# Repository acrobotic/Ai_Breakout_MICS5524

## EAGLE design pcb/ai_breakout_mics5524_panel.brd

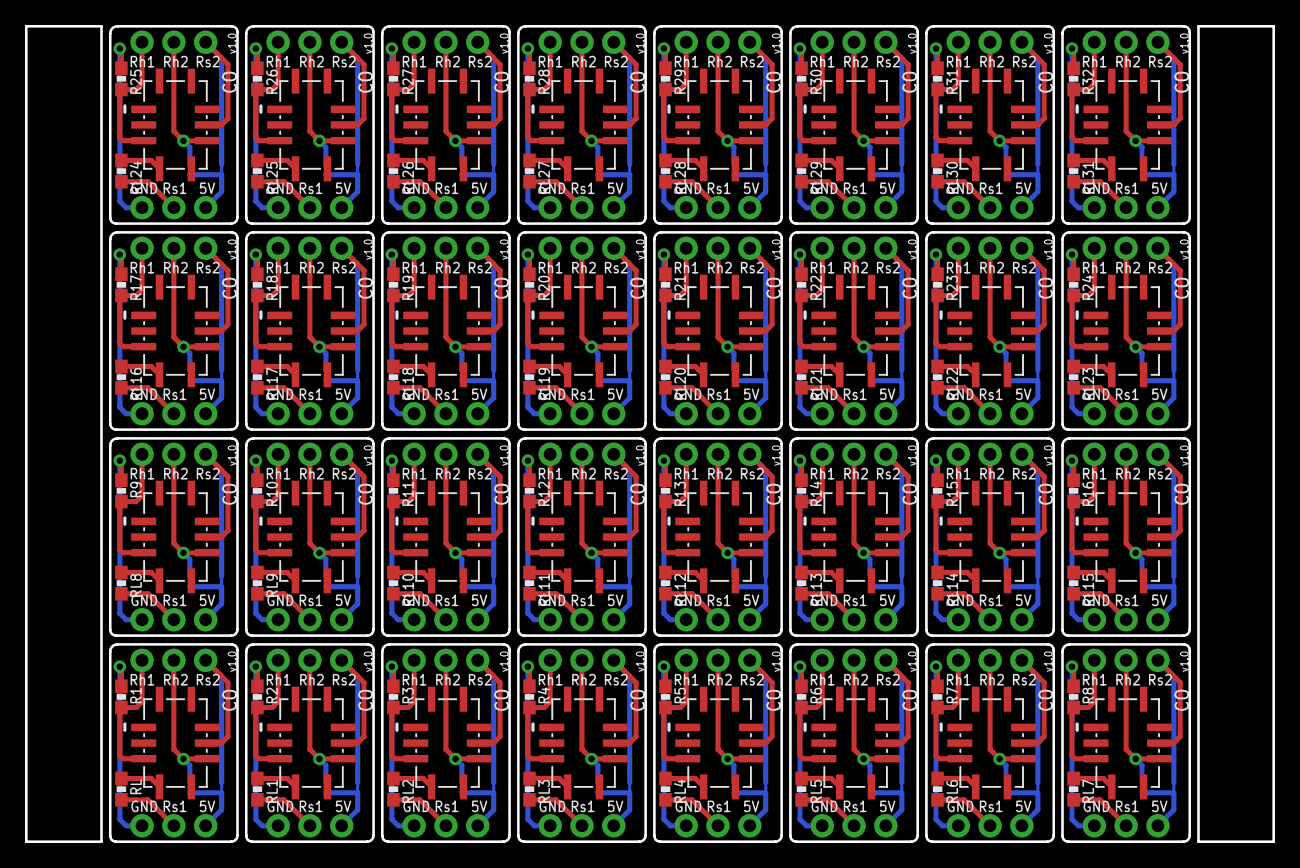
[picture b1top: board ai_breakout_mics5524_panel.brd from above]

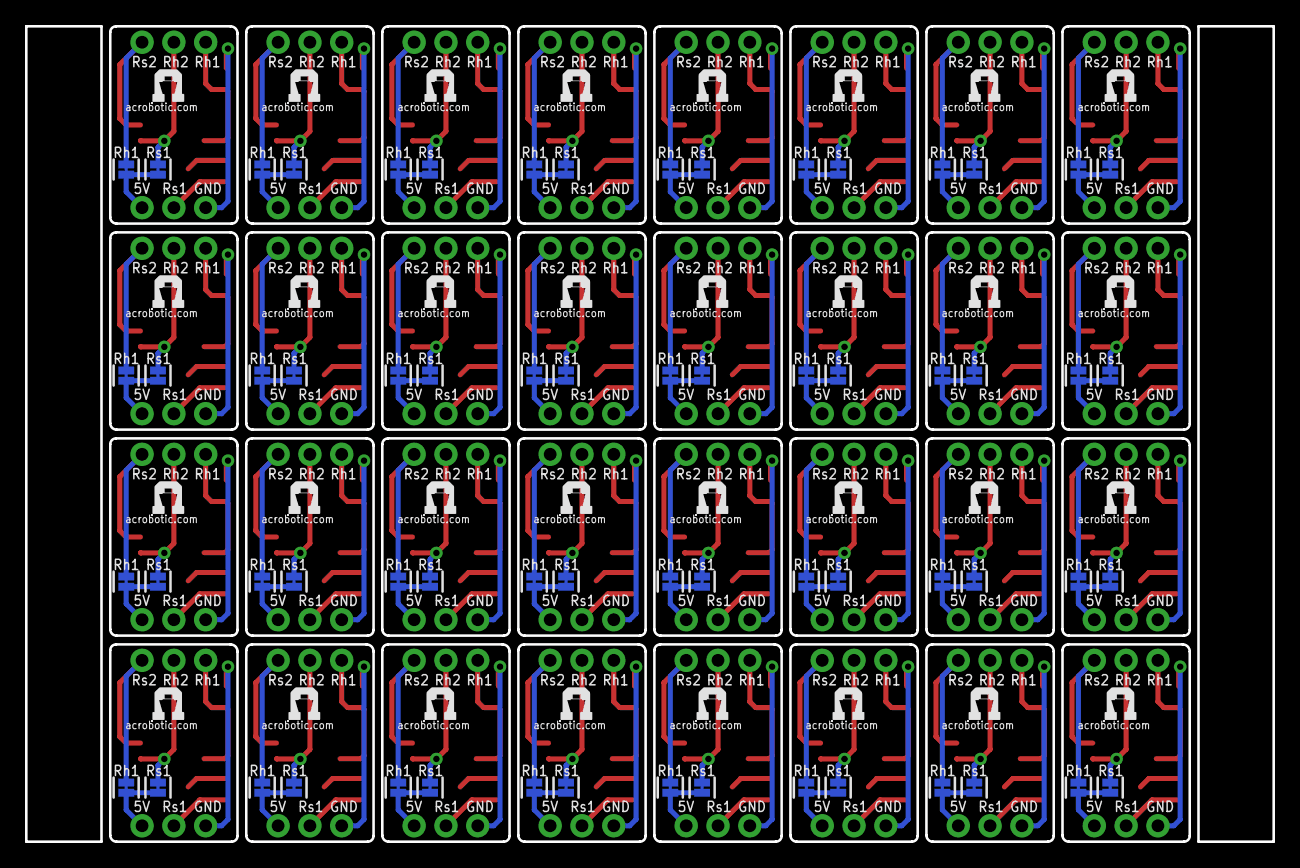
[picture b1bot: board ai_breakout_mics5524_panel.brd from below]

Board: 2 copper layers, 99.6 x 65.1 mm, 256 parts (96 on the bottom side), 224 nets.

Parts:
J1, J2, J3, J4, J5, J6, J7, J8, J9, J10, J11, J12, J13, J14, J15, J16, J17, J18, J19, J20, J21, J22, J23, J24, J25, J26, J27, J28, J29, J30, J31, J32, J33, J34, J35, J36, J37, J38, J39, J40, J41, J42, J43, J44, J45, J46, J47, J48, J49, J50, J51, J52, J53, J54, J55, J56, J57, J58, J59, J60, J61, J62, J63, J64: 1X03NOFIRST; 1X03-NOFIRST
JS1, JS2, JS3, JS4, JS5, JS6, JS7, JS8, JS9, JS10, JS11, JS12, JS13, JS14, JS15, JS16, JS17, JS18, JS19, JS20, JS21, JS22, JS23, JS24, JS25, JS26, JS27, JS28, JS29, JS30, JS31, JS32, JS33, JS34, JS35, JS36, JS37, JS38, JS39, JS40, JS41, JS42, JS43, JS44, JS45, JS46, JS47, JS48, JS49, JS50, JS51, JS52, JS53, JS54, JS55, JS56, JS57, JS58, JS59, JS60, JS61, JS62, JS63, JS64: 1X02-SJ-NCT
R1, R2, R3, R4, R5, R6, R7, R8, R9, R10, R11, R12, R13, R14, R15, R16, R17, R18, R19, R20, R21, R22, R23, R24, R25, R26, R27, R28, R29, R30, R31, R32: 82; RES-0603
RL, RL1, RL2, RL3, RL4, RL5, RL6, RL7, RL8, RL9, RL10, RL11, RL12, RL13, RL14, RL15, RL16, RL17, RL18, RL19, RL20, RL21, RL22, RL23, RL24, RL25, RL26, RL27, RL28, RL29, RL30, RL31: 820; RES-0603
U1, U2, U3, U4, U5, U6, U7, U8, U9, U10, U11, U12, U13, U14, U15, U16, U17, U18, U19, U20, U21, U22, U23, U24, U25, U26, U27, U28, U29, U30, U31, U32: MICS-5524; MICS-SMD10
U$1, U$2, U$3, U$4, U$5, U$6, U$7, U$8, U$9, U$10, U$11, U$12, U$13, U$14, U$15, U$16, U$17, U$18, U$19, U$20, U$21, U$22, U$23, U$24, U$25, U$26, U$27, U$28, U$29, U$30, U$31, U$32: AI-LOGOXS; AI-LOGO-XS

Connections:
5V: J2.1, JS1.2, JS2.2
5V1: J4.1, JS3.2, JS4.2
5V2: J6.1, JS5.2, JS6.2
5V3: J8.1, JS7.2, JS8.2
5V4: J10.1, JS9.2, JS10.2
5V5: J12.1, JS11.2, JS12.2
5V6: J14.1, JS13.2, JS14.2
5V7: J16.1, JS15.2, JS16.2
5V8: J18.1, JS17.2, JS18.2
5V9: J20.1, JS19.2, JS20.2
5V10: J22.1, JS21.2, JS22.2
5V11: J24.1, JS23.2, JS24.2
5V12: J26.1, JS25.2, JS26.2
5V13: J28.1, JS27.2, JS28.2
5V14: J30.1, JS29.2, JS30.2
5V15: J32.1, JS31.2, JS32.2
5V16: J34.1, JS33.2, JS34.2
5V17: J36.1, JS35.2, JS36.2
5V18: J38.1, JS37.2, JS38.2
5V19: J40.1, JS39.2, JS40.2
5V20: J42.1, JS41.2, JS42.2
5V21: J44.1, JS43.2, JS44.2
5V22: J46.1, JS45.2, JS46.2
5V23: J48.1, JS47.2, JS48.2
5V24: J50.1, JS49.2, JS50.2
5V25: J52.1, JS51.2, JS52.2
5V26: J54.1, JS53.2, JS54.2
5V27: J56.1, JS55.2, JS56.2
5V28: J58.1, JS57.2, JS58.2
5V29: J60.1, JS59.2, JS60.2
5V30: J62.1, JS61.2, JS62.2
5V31: J64.1, JS63.2, JS64.2
A/RH1: J1.3, R1.2, U2.C
A/RH2: J3.3, R2.2, U1.C
A/RH3: J5.3, R3.2, U3.C
A/RH4: J7.3, R4.2, U4.C
A/RH5: J9.3, R5.2, U5.C
A/RH6: J11.3, R6.2, U6.C
A/RH7: J13.3, R7.2, U7.C
A/RH8: J15.3, R8.2, U8.C
A/RH9: J17.3, R9.2, U9.C
A/RH10: J19.3, R10.2, U10.C
A/RH11: J21.3, R11.2, U11.C
A/RH12: J23.3, R12.2, U12.C
A/RH13: J25.3, R13.2, U13.C
A/RH14: J27.3, R14.2, U14.C
A/RH15: J29.3, R15.2, U15.C
A/RH16: J31.3, R16.2, U16.C
A/RH17: J33.3, R17.2, U17.C
A/RH18: J35.3, R18.2, U18.C
A/RH19: J37.3, R19.2, U19.C
A/RH20: J39.3, R20.2, U20.C
A/RH21: J41.3, R21.2, U21.C
A/RH22: J43.3, R22.2, U22.C
A/RH23: J45.3, R23.2, U23.C
A/RH24: J47.3, R24.2, U24.C
A/RH25: J49.3, R25.2, U25.C
A/RH26: J51.3, R26.2, U26.C
A/RH27: J53.3, R27.2, U27.C
A/RH28: J55.3, R28.2, U28.C
A/RH29: J57.3, R29.2, U29.C
A/RH30: J59.3, R30.2, U30.C
A/RH31: J61.3, R31.2, U31.C
A/RH32: J63.3, R32.2, U32.C
B/RS1: J2.2, RL.2
B/RS2: J4.2, RL1.2
B/RS3: J6.2, RL2.2
B/RS4: J8.2, RL3.2
B/RS5: J10.2, RL4.2
B/RS6: J12.2, RL5.2
B/RS7: J14.2, RL6.2
B/RS8: J16.2, RL7.2
B/RS9: J18.2, RL8.2
B/RS10: J20.2, RL9.2
B/RS11: J22.2, RL10.2
B/RS12: J24.2, RL11.2
B/RS13: J26.2, RL12.2
B/RS14: J28.2, RL13.2
B/RS15: J30.2, RL14.2
B/RS16: J32.2, RL15.2
B/RS17: J34.2, RL16.2
B/RS18: J36.2, RL17.2
B/RS19: J38.2, RL18.2
B/RS20: J40.2, RL19.2
B/RS21: J42.2, RL20.2
B/RS22: J44.2, RL21.2
B/RS23: J46.2, RL22.2
B/RS24: J48.2, RL23.2
B/RS25: J50.2, RL24.2
B/RS26: J52.2, RL25.2
B/RS27: J54.2, RL26.2
B/RS28: J56.2, RL27.2
B/RS29: J58.2, RL28.2
B/RS30: J60.2, RL29.2
B/RS31: J62.2, RL30.2
B/RS32: J64.2, RL31.2
GND: J2.3, R1.1
GND1: J4.3, R2.1
GND2: J6.3, R3.1
GND3: J8.3, R4.1
GND4: J10.3, R5.1
GND5: J12.3, R6.1
GND6: J14.3, R7.1
GND7: J16.3, R8.1
GND8: J18.3, R9.1
GND9: J20.3, R10.1
GND10: J22.3, R11.1
GND11: J24.3, R12.1
GND12: J26.3, R13.1
GND13: J28.3, R14.1
GND14: J30.3, R15.1
GND15: J32.3, R16.1
GND16: J34.3, R17.1
GND17: J36.3, R18.1
GND18: J38.3, R19.1
GND19: J40.3, R20.1
GND20: J42.3, R21.1
GND21: J44.3, R22.1
GND22: J46.3, R23.1
GND23: J48.3, R24.1
GND24: J50.3, R25.1
GND25: J52.3, R26.1
GND26: J54.3, R27.1
GND27: J56.3, R28.1
GND28: J58.3, R29.1
GND29: J60.3, R30.1
GND30: J62.3, R31.1
GND31: J64.3, R32.1
H/RH1: J3.2, JS4.1, U1.F
H/RH2: J1.2, JS2.1, U2.F
H/RH3: J5.2, JS6.1, U3.F
H/RH4: J7.2, JS8.1, U4.F
H/RH5: J9.2, JS10.1, U5.F
H/RH6: J11.2, JS12.1, U6.F
H/RH7: J13.2, JS14.1, U7.F
H/RH8: J15.2, JS16.1, U8.F
H/RH9: J17.2, JS18.1, U9.F
H/RH10: J19.2, JS20.1, U10.F
H/RH11: J21.2, JS22.1, U11.F
H/RH12: J23.2, JS24.1, U12.F
H/RH13: J25.2, JS26.1, U13.F
H/RH14: J27.2, JS28.1, U14.F
H/RH15: J29.2, JS30.1, U15.F
H/RH16: J31.2, JS32.1, U16.F
H/RH17: J33.2, JS34.1, U17.F
H/RH18: J35.2, JS36.1, U18.F
H/RH19: J37.2, JS38.1, U19.F
H/RH20: J39.2, JS40.1, U20.F
H/RH21: J41.2, JS42.1, U21.F
H/RH22: J43.2, JS44.1, U22.F
H/RH23: J45.2, JS46.1, U23.F
H/RH24: J47.2, JS48.1, U24.F
H/RH25: J49.2, JS50.1, U25.F
H/RH26: J51.2, JS52.1, U26.F
H/RH27: J53.2, JS54.1, U27.F
H/RH28: J55.2, JS56.1, U28.F
H/RH29: J57.2, JS58.1, U29.F
H/RH30: J59.2, JS60.1, U30.F
H/RH31: J61.2, JS62.1, U31.F
H/RH32: J63.2, JS64.1, U32.F
J/RS1: J3.1, JS3.1, U1.G
J/RS2: J1.1, JS1.1, U2.G
J/RS3: J5.1, JS5.1, U3.G
J/RS4: J7.1, JS7.1, U4.G
J/RS5: J9.1, JS9.1, U5.G
J/RS6: J11.1, JS11.1, U6.G
J/RS7: J13.1, JS13.1, U7.G
J/RS8: J15.1, JS15.1, U8.G
J/RS9: J17.1, JS17.1, U9.G
J/RS10: J19.1, JS19.1, U10.G
J/RS11: J21.1, JS21.1, U11.G
J/RS12: J23.1, JS23.1, U12.G
J/RS13: J25.1, JS25.1, U13.G
J/RS14: J27.1, JS27.1, U14.G
J/RS15: J29.1, JS29.1, U15.G
J/RS16: J31.1, JS31.1, U16.G
J/RS17: J33.1, JS33.1, U17.G
J/RS18: J35.1, JS35.1, U18.G
J/RS19: J37.1, JS37.1, U19.G
J/RS20: J39.1, JS39.1, U20.G
J/RS21: J41.1, JS41.1, U21.G
J/RS22: J43.1, JS43.1, U22.G
J/RS23: J45.1, JS45.1, U23.G
J/RS24: J47.1, JS47.1, U24.G
J/RS25: J49.1, JS49.1, U25.G
J/RS26: J51.1, JS51.1, U26.G
J/RS27: J53.1, JS53.1, U27.G
J/RS28: J55.1, JS55.1, U28.G
J/RS29: J57.1, JS57.1, U29.G
J/RS30: J59.1, JS59.1, U30.G
J/RS31: J61.1, JS61.1, U31.G
J/RS32: J63.1, JS63.1, U32.G
unnamed: RL.1, U2.D
unnamed: RL1.1, U1.D
unnamed: RL2.1, U3.D
unnamed: RL3.1, U4.D
unnamed: RL4.1, U5.D
unnamed: RL5.1, U6.D
unnamed: RL6.1, U7.D
unnamed: RL7.1, U8.D
unnamed: RL8.1, U9.D
unnamed: RL9.1, U10.D
unnamed: RL10.1, U11.D
unnamed: RL11.1, U12.D
unnamed: RL12.1, U13.D
unnamed: RL13.1, U14.D
unnamed: RL14.1, U15.D
unnamed: RL15.1, U16.D
unnamed: RL16.1, U17.D
unnamed: RL17.1, U18.D
unnamed: RL18.1, U19.D
unnamed: RL19.1, U20.D
unnamed: RL20.1, U21.D
unnamed: RL21.1, U22.D
unnamed: RL22.1, U23.D
unnamed: RL23.1, U24.D
unnamed: RL24.1, U25.D
unnamed: RL25.1, U26.D
unnamed: RL26.1, U27.D
unnamed: RL27.1, U28.D
unnamed: RL28.1, U29.D
unnamed: RL29.1, U30.D
unnamed: RL30.1, U31.D
unnamed: RL31.1, U32.D
